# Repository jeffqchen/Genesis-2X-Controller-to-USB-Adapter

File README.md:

# Genesis 2X Controller to USB Adapter

This is my take on the Genesis 2X Controller to USB Adapter, powered by [DaemonBite](https://github.com/MickGyver/DaemonBite-Retro-Controllers-USB).

----------

## Parts

- [PCB](https://oshpark.com/shared_projects/lUJ4HBFS)

- DB9 Ports (Choose the DR9, Male option) - [Link](https://github.com/jeffqchen/JeffParts/blob/main/Connectors/DB9/Male%20PCB/info.md)

- Arduino Pro Micro 5V/16MHz Version - [Link](https://github.com/jeffqchen/JeffParts/blob/main/Board/Arduino/Pro%20Micro/5V%2016MHz/info.md)

- [2x] 2.54mm Pitch Pin Header, Square Pins, Single Row - 12 pins on each side - [Link](https://github.com/jeffqchen/JeffParts/blob/main/Connectors/Pin%20Header/2.54mm%20Pitch/Male%20Straight/info.md)

- [2x] M2x20mm Hex Screw & Nut - [Link](https://github.com/jeffqchen/JeffParts/blob/main/Parts/M2%20M3%20Hex%20Screw%20%26%20Nut/info.md)

- 3D Printed Shell

---------

## 3D Printing

Print the two halves of the shell in their original orientation.

Suggested settings:
- 0.16 layer height
- 0.35 line width
- With support

-----------

## Assembly

Trim all the extra stubs from the PCB.

Loosen the screws on both sides of the DB9 ports, but don't remove them yet.

Solder in the DB9 ports first. Then the Pro Micro on the other side with the pin headers. Trim the protruding pin header pins on the other side of the PCB. Otherwise you won't be able to fit the assembly into the shell.

Remove the screws and the face plate from the DB9 port. Otherwise you won't be able to fit the assembly into the shell.

Finally, slide the assembly into the printed shell, and screw it shut with two sets of M2x20mm hex screws and nuts.

-----------
Shield: [![CC BY-SA 4.0][cc-by-sa-shield]][cc-by-sa]

This work is licensed under a
[Creative Commons Attribution-ShareAlike 4.0 International License][cc-by-sa].

[![CC BY-SA 4.0][cc-by-sa-image]][cc-by-sa]

[cc-by-sa]: http://creativecommons.org/licenses/by-sa/4.0/
[cc-by-sa-image]: https://licensebuttons.net/l/by-sa/4.0/88x31.png
[cc-by-sa-shield]: https://img.shields.io/badge/License-CC%20BY--SA%204.0-lightgrey.svg

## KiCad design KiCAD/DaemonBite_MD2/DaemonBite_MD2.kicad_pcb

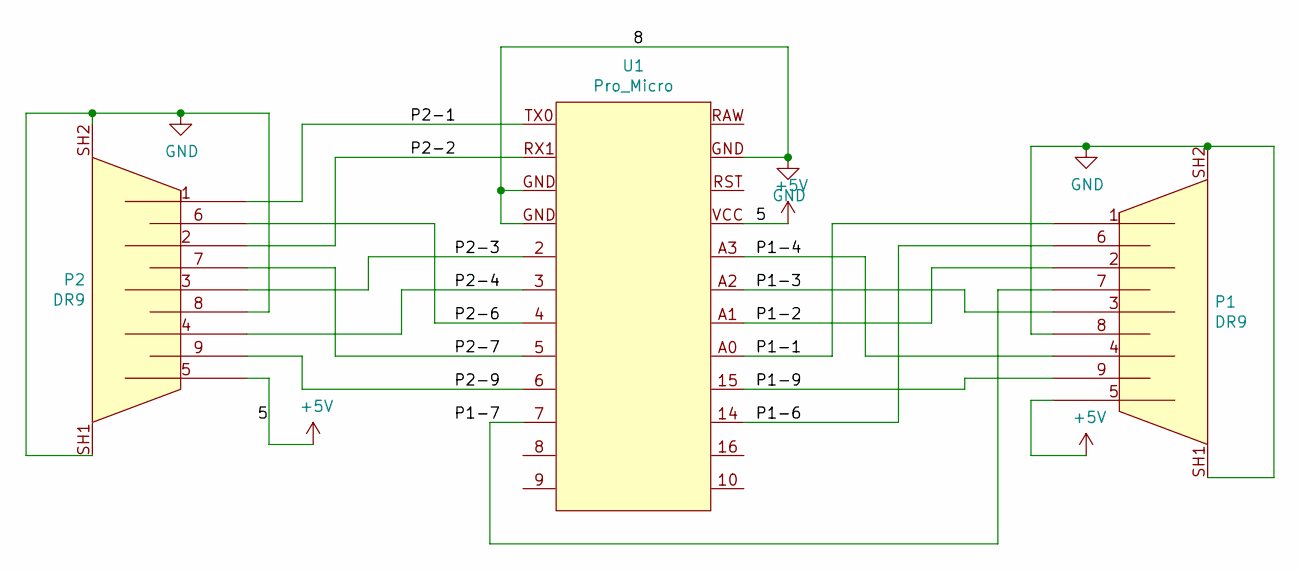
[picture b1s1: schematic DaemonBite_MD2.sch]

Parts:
P1, P2: DR9; DR9_Male_PCB
U1: Pro_Micro

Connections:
+5V: P1.5, P2.5, U1.VCC
/P1-1: P1.1, U1.A0
/P1-2: P1.2, U1.A1
/P1-3: P1.3, U1.A2
/P1-4: P1.4, U1.A3
/P1-6: P1.6, U1.14
/P1-7: P1.7, U1.7
/P1-9: P1.9, U1.15
/P2-1: P2.1, U1.TX0
/P2-2: P2.2, U1.RX1
/P2-3: P2.3, U1.2
/P2-4: P2.4, U1.3
/P2-6: P2.6, U1.4
/P2-7: P2.7, U1.5
/P2-9: P2.9, U1.6
GND: P1.8, P1.SH1, P1.SH2, P2.8, P2.SH1, P2.SH2, U1.GND

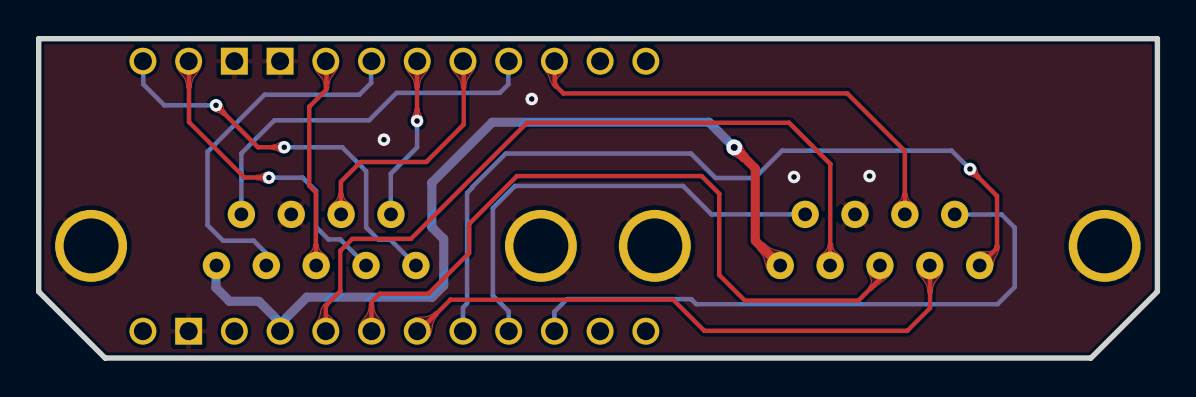
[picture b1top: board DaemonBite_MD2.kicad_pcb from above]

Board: 2 copper layers, 62.2 x 17.7 mm, 3 parts (1 on the bottom side), 16 nets.

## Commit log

2021-10-27 test
    111
2021-10-27 Initial Upload
2022-08-09 Change license type
